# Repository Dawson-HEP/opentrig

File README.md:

# opentrig

> ***open***-source ***trig***ger system

An open-source, integrated, particle physics data acquisition system (DAQ).

Designed to interface with timing systems controlled by the [AIDA-2020 TLU](https://gitlab.com/ohwr/project/fmc-mtlu).
Up to 24 digital trigger channels with variable-gain threshold setting.

## Features

- 144 MHz internal FPGA clock, and timing resolution
- 24 digital trigger channels with variable gain
- Input voltage range 3.3V-5V
- TTL level compatible clock, trigger, input and output
- [AIDA-2020 TLU synchronous AIDA mode](https://gitlab.com/ohwr/project/fmc-mtlu/-/raw/master/Documentation/Main_TLU.pdf?ref_type=heads) (page 31) compatible FPGA

## Hardware Overview

[**Schematics can be found here.**](hardware/digital.pdf)

Front panel IO (left)
- Input clock signal (<40 MHz square wave)
- Output clock signal (120 MHz square wave, 3.3V TTL, <0.5% jitter, phase-locked)
- Input/output trigger (3.3V TTL)
- Input/output veto (3.3V TTL)
- Extra 50R impedance-matched inputs

Back panel (right)
- 24 channel digital inputs, with variable trigger thresholds (1.024 mV steps):
    - 0.000V-2.000V (1x gain)
    - 0.000V-4.000V (2x gain)

Internal components
- Low drift 5.000V reference (TI REF5050AIR)
- 12 high-speed thresholding comparators (TI TLV3502)
- 120 MHz MCU (RP2040)
- FPGA (Lattice ICE40 HX4K)

## Trigger Architecture

The *opentrig* system is a 24-channel, synchronous data acquisition platform compatible with EUDAQ2-compatible beamline trigger systems. Each channel digitizes an analog falling-edge into a digital rising-edge depending on a threshold set by independent digital-to-analog converters (DACs). Three trigger sources are fed into a selectable OR-ing gate, which allows for the selection of the interrupt source(s) for sample recording.

The trigger combiner vetoes priority in regards to the inputs of selected trigger sources, and assigns FPGA SPI bandwidth to the microcontroller (MCU) for processing and sampling. An active-high trigger output is asserted with controllable duration and delay in reference to the trigger sources. The sample interrupt interacts with the MCU in order to stream data live through the USB Type-C interface across bulk transfer.

### Trigger Delay

The delays incurred by the trigger is synchronized across channels by means of length matching. The largest skew is a result of level shifting: indeed up to $\pm 0.3$ ns across channels. No significant differences are measured in practice. FPGA gate skew is below the delays of level shifting, and are thus negligible in practice. PCB traces are delay-matched to within $\pm0.01$ mm. Given the assumption that channels are synchronized between each other, the input-output delay needs to be considered.

## Clocks

The FPGA PLL is synchronized to a sampling clock of $120$ MHz, while the SPI clock transfers data at a rate of $5$ MHz. The user can select an internal clock input or an external clock input, both requiring different PLL clock dividers to achieve the full sampling rate at $120$ Msps.

Clocks are phase-aligned by phase-locked-loop (PLL). An internal clock can be generated for the independent functioning of the DAQ. Proper PLL clock dividers and multipliers must be set to achieve the target $120$ MHz. An external clock compliant to EUDAQ2 trigger systems, such as the AIDA-2020 TLU, can be synchronized to \textit{opentrig}. A 16-bit trigger-ID can be read synchronously by the phase-locked external trigger module, which will be recorded upon the assertion of a sample interrupt.

## Voltage Levels

The 24 analog inputs are limited to a voltage range of $-0.30$ V to $+5.30$ V on wide-gain mode, and $-0.30$ V to $+3.30$ V on limited-gain mode. A voltage beyond permissible levels may cause irreversible damage to thresholding comparators, whose inputs are directly connected to SMA connectors.

The digital signals are high-impedance or $50 \Omega$ terminated depending on the label, and function on $3.3$ V CMOS voltage levels. The push-pull drivers have weak drive capabilities; therefore, only small digital loads may be attached with matched impedance.

## Directory Structure

The hardware is designed in [KiCad](https://www.kicad.org/) for the digital trigger front-end and mechanical layout, while the firmware and control utilities are written in [Rust](https://rust-lang.org/) using the [Embassy](https://embassy.dev/) embedded framework. The FPGA subsystems are written in pure Verilog with the [Yosys](https://github.com/YosysHQ/yosys.git) open-source toolchain, and [Project Icestorm](https://github.com/YosysHQ/icestorm)'s bitstream documentation.

```
opentrig/
├── hardware/ # KiCad hardware design
│   ├── fab/ # Fabrication files and gerbers
│   ├── logos.pretty/ # Custom logo footprints and graphics
│   └── digital.pretty/ # Custom digital footprints and component libraries
│
├── opentrig/ # Core DAQ firmware
│   ├── src/ # Source code (Rust + Embassy)
│   │   └── fpga/ # FPGA interface and logic modules
│   └── target/ # Compiled firmware output and build artifacts
│
├── cli/ # Command-line interface for control and configuration via host computer
│   ├── src/ # Rust source for CLI utilities
│   └── target/ # Compiled CLI binaries
│
├── tests/ # Automated and hardware-in-the-loop test framework
│   ├── src/ # Unit and integration test sources
│   └── target/ # Compiled test binaries and reports
│
└── README.md # Project overview, setup, and usage instructions
```

## Building

Before building the firmware and FPGA bitstream, you need to install a few dependencies for Rust and the FPGA toolchain. Follow these steps:

- Install [Rust](https://www.rust-lang.org/) – the firmware is written in Rust using the Embassy framework.
- Install [Just](https://github.com/casey/just) – used to run the build commands.
- Install [Yosys](https://github.com/YosysHQ/yosys) – for Verilog synthesis of the FPGA.
- Install [Project Icestorm](https://github.com/YosysHQ/icestorm) tools – for routing and bitstream generation for iCE40 FPGAs.
- Optional: [KiCad](https://www.kicad.org/) – for viewing and editing hardware schematics.

Once dependencies are installed, clone the repository, navigate to the firmware folder, and run the build commands:

```bash
# Clone the Protovolt repository from GitHub
git clone https://github.com/Dawson-HEP/opentrig.git

# Go to firmware directory
cd opentrig/opentrig
```

```bash
# Compile verilog bitstream
just build-verilog

# Compile embedded firmware
just build-rust
```

Flashing:
- SWD debug port on the PCB
- USB flashing via data port

## Running the DAQ
A USB Type-C Power Delivery (PD) supply must be connected to the power connector to bias analog and digital circuitry. A $100$ W-capable supply with $20$V output is preferred to provide enough margin for buck converters and analog filtering supplies to function properly. A digital data cable links the data acquisition computer with the DAQ.

## Debugging the DAQ
Three SWD debug interfaces are made available to the user: the main *opentrig* MCU debug link, the simulation PICO link, and the logic analyzer PICO link. The MCU flash process includes the FPGA bitstream, which is written upon power up of the DAQ. The simulation PICO, when powered, produce triggers via the internal links directly to the FPGA, which allows for programmatic debugging. The logic analyzer serves as a bitstream debugger, where internal registers and wires can be sampled.

## DESY Test Beam

The interfacing with the AIDA-2020 TLU functionality has been verified at the [DESY II Test Beam facility](https://desy.de/index_eng.html) in September of 2025, as part of the [Beamline for Schools](https://beamlineforschools.cern/) Competition. 

*Testbeam Area 21, Translation Stage*

## Gallery

## License

This project is open-source under the Eclipse Public License - v 2.0.

## Authors

- [Tian Yi, Xia](https://github.com/ThatAquarel), xtxiatianyi@gmail.com
- [Leandro Perez-Moran](https://github.com/LudioRex), pemle2007@gmail.com

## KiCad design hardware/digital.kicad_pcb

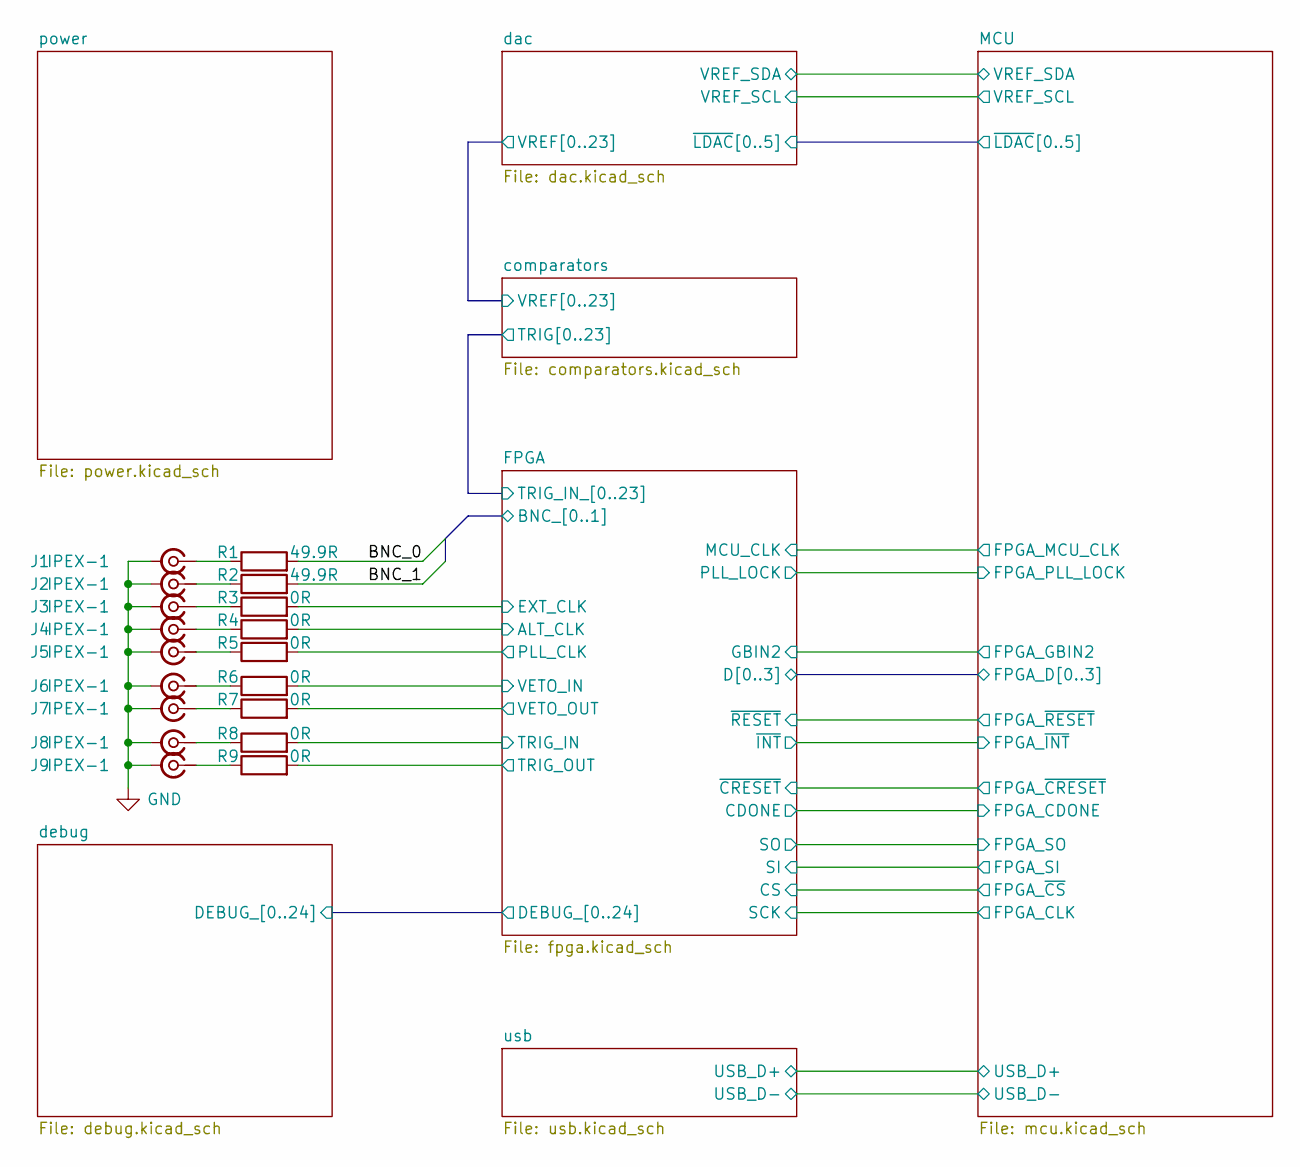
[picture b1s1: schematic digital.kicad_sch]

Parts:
J1, J2, J3, J4, J5, J6, J7, J8, J9: IPEX-1; BWIPX-1-001E; LCSC C496552
R1, R2: 49.9R; R_0402_1005Metric; LCSC C17168
R3, R4, R5, R6, R7, R8, R9: 0R; R_0402_1005Metric; LCSC C17168

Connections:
/FPGA/ALT_CLK: R4.2; also elsewhere on the board
/FPGA/BNC_0: R1.2; also elsewhere on the board
/FPGA/BNC_1: R2.2; also elsewhere on the board
/FPGA/EXT_CLK: R3.2; also elsewhere on the board
/FPGA/PLL_CLK: R5.2; also elsewhere on the board
/FPGA/TRIG_IN: R8.2; also elsewhere on the board
/FPGA/TRIG_OUT: R9.2; also elsewhere on the board
/FPGA/VETO_IN: R6.2; also elsewhere on the board
/FPGA/VETO_OUT: R7.2; also elsewhere on the board
GND: J1.2 (Ext), J2.2 (Ext), J3.2 (Ext), J4.2 (Ext), J5.2 (Ext), J6.2 (Ext), J7.2 (Ext), J8.2 (Ext), J9.2 (Ext); also elsewhere on the board
unnamed: J1.1 (In), R1.1
unnamed: J2.1 (In), R2.1
unnamed: J3.1 (In), R3.1
unnamed: J4.1 (In), R4.1
unnamed: J5.1 (In), R5.1
unnamed: J6.1 (In), R6.1
unnamed: J7.1 (In), R7.1
unnamed: J8.1 (In), R8.1
unnamed: J9.1 (In), R9.1

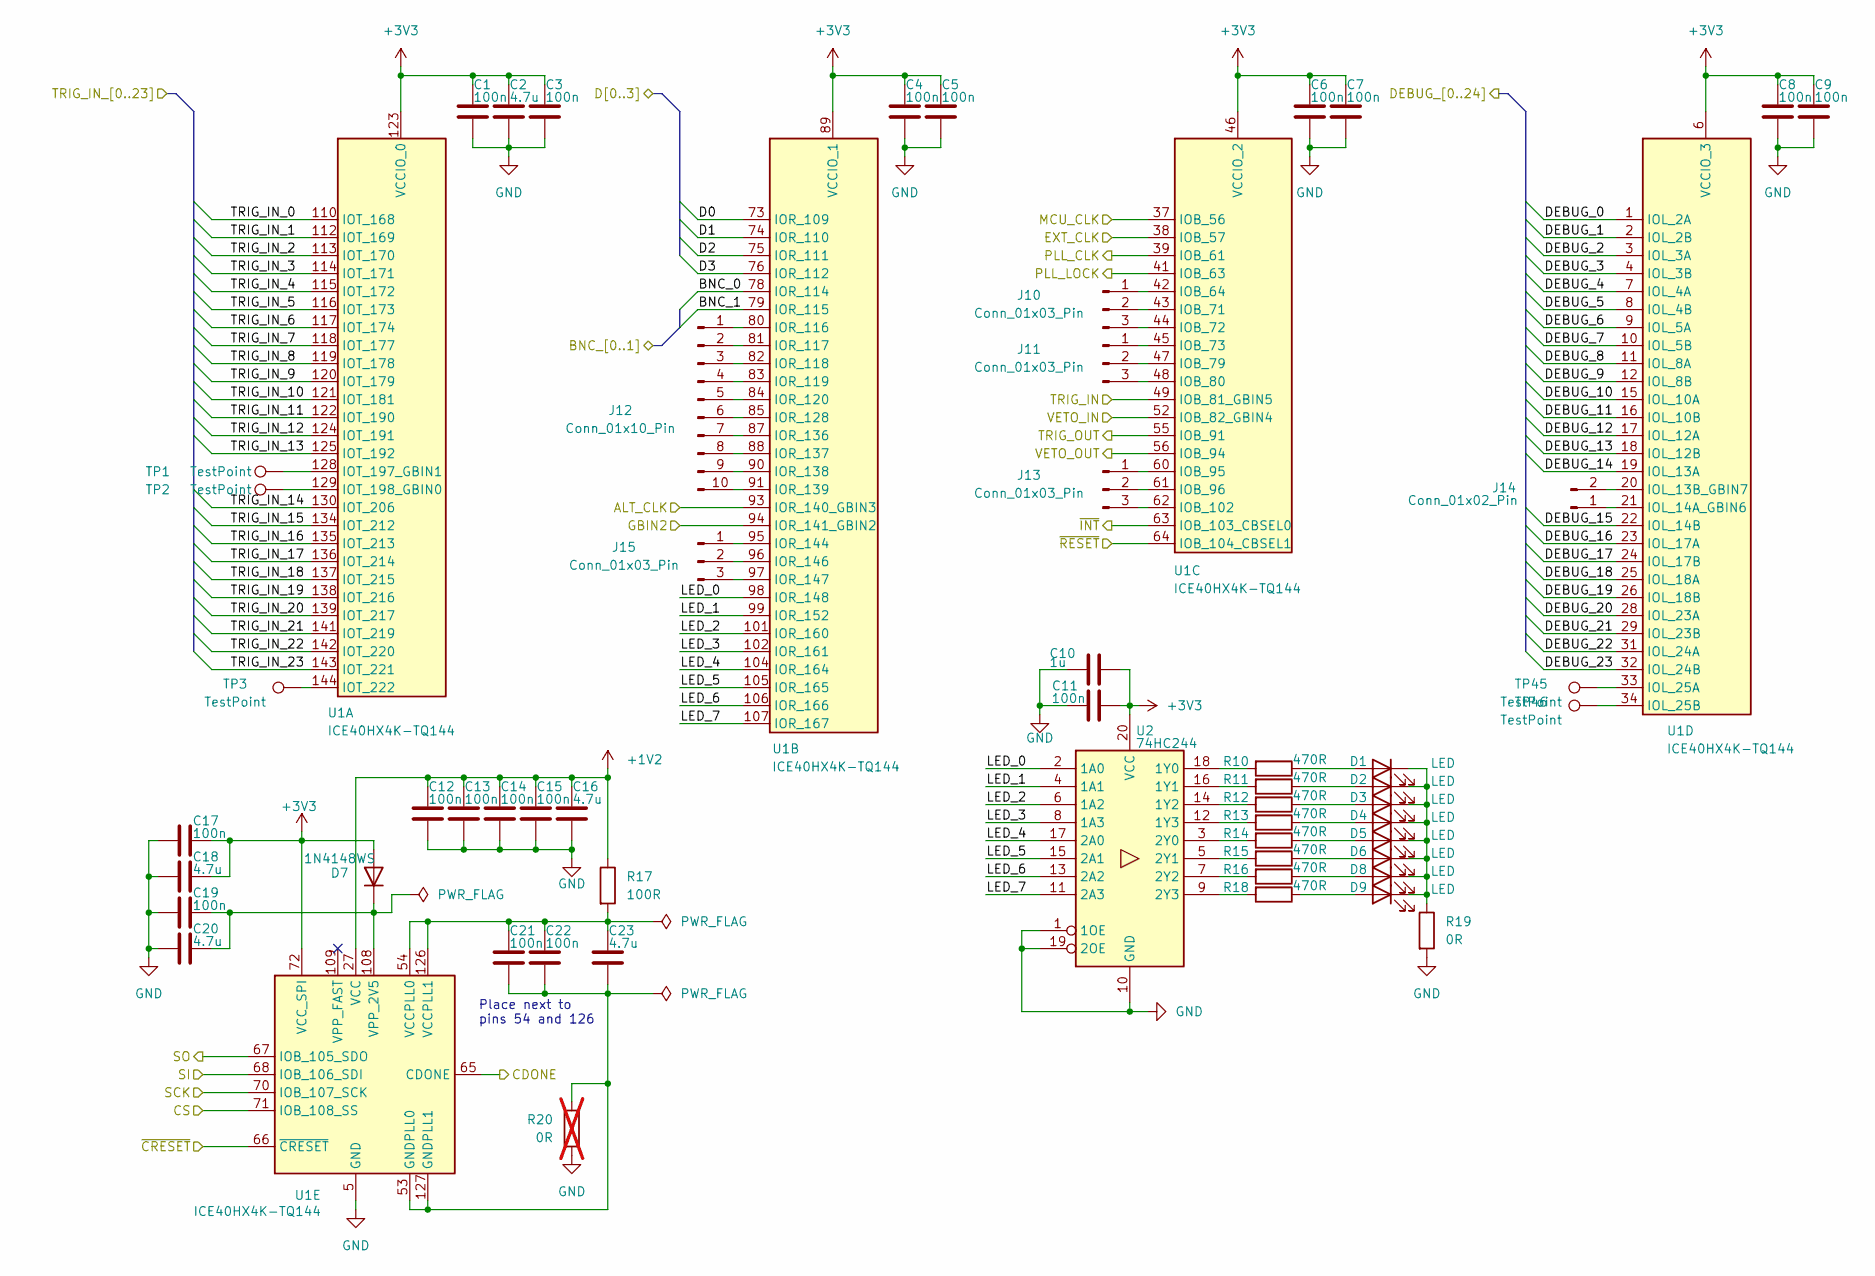
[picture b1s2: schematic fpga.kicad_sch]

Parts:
C1, C3, C4, C5, C6, C7, C8, C9, C11, C12, C13, C14, C15, C17, C19, C21, C22: 100n; C_0402_1005Metric; LCSC C307331
C2, C16, C18, C20, C23: 4.7u; C_1206_3216Metric; LCSC C29823
C10: 1u; C_0805_2012Metric; LCSC C28323
D1, D2, D3, D4, D5, D6, D8, D9: LED; LED_0805_2012Metric; LCSC C2297
D7: 1N4148WS; D_SOD-323; LCSC C2128
J10, J11, J13, J15: Conn_01x03_Pin; PinHeader_1x03_P1.00mm_Vertical_SMD_Pin1Left
J12: Conn_01x10_Pin; PinHeader_1x10_P1.00mm_Vertical_SMD_Pin1Left
J14: Conn_01x02_Pin; PinHeader_1x02_P1.00mm_Vertical_SMD_Pin1Left
R10, R11, R12, R13, R14, R15, R16, R18: 470R; R_0402_1005Metric; LCSC C25117
R17: 100R; R_0402_1005Metric; LCSC C25076
R19: 0R; R_0402_1005Metric; LCSC C17168
R20: 0R; R_0402_1005Metric; not fitted
TP1, TP2, TP3, TP45, TP46: TestPoint; TestPoint_Pad_D1.0mm
U1: ICE40HX4K-TQ144; TQFP-144_20x20mm_P0.5mm
U2: 74HC244; TSSOP-20_4.4x6.5mm_P0.65mm; LCSC C6835

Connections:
+1V2: C12.1, C13.1, C14.1, C15.1, C16.1, R17.1, U1.27 (VCC), U1.40 (VCC), U1.92 (VCC), U1.111 (VCC); also elsewhere on the board
+3V3: C1.1, C2.1, C3.1, C4.1, C5.1, C6.1, C7.1, C8.1, C9.1, C10.2, C11.2, C17.1, C18.1, D7.2 (A), U1.6 (VCCIO_3), U1.30 (VCCIO_3), U1.46 (VCCIO_2), U1.57 (VCCIO_2), U1.72 (VCC_SPI), U1.89 (VCCIO_1), U1.100 (VCCIO_1), U1.123 (VCCIO_0), U1.131 (VCCIO_0), U2.20 (VCC); also elsewhere on the board
/FPGA/ALT_CLK: U1.93 (IOR_140_GBIN3); also elsewhere on the board
/FPGA/BNC_0: U1.78 (IOR_114); also elsewhere on the board
/FPGA/BNC_1: U1.79 (IOR_115); also elsewhere on the board
/FPGA/CDONE: U1.65 (CDONE); also elsewhere on the board
/FPGA/CS: U1.71 (IOB_108_SS); also elsewhere on the board
/FPGA/D0: U1.73 (IOR_109); also elsewhere on the board
/FPGA/D1: U1.74 (IOR_110); also elsewhere on the board
/FPGA/D2: U1.75 (IOR_111); also elsewhere on the board
/FPGA/D3: U1.76 (IOR_112); also elsewhere on the board
/FPGA/DEBUG_0: U1.1 (IOL_2A); also elsewhere on the board
/FPGA/DEBUG_1: U1.2 (IOL_2B); also elsewhere on the board
/FPGA/DEBUG_2: U1.3 (IOL_3A); also elsewhere on the board
/FPGA/DEBUG_3: U1.4 (IOL_3B); also elsewhere on the board
/FPGA/DEBUG_4: U1.7 (IOL_4A); also elsewhere on the board
/FPGA/DEBUG_5: U1.8 (IOL_4B); also elsewhere on the board
/FPGA/DEBUG_6: U1.9 (IOL_5A); also elsewhere on the board
/FPGA/DEBUG_7: U1.10 (IOL_5B); also elsewhere on the board
/FPGA/DEBUG_8: U1.11 (IOL_8A); also elsewhere on the board
/FPGA/DEBUG_9: U1.12 (IOL_8B); also elsewhere on the board
/FPGA/DEBUG_10: U1.15 (IOL_10A); also elsewhere on the board
/FPGA/DEBUG_11: U1.16 (IOL_10B); also elsewhere on the board
/FPGA/DEBUG_12: U1.17 (IOL_12A); also elsewhere on the board
/FPGA/DEBUG_13: U1.18 (IOL_12B); also elsewhere on the board
/FPGA/DEBUG_14: U1.19 (IOL_13A); also elsewhere on the board
/FPGA/DEBUG_15: U1.22 (IOL_14B); also elsewhere on the board
/FPGA/DEBUG_16: U1.23 (IOL_17A); also elsewhere on the board
/FPGA/DEBUG_17: U1.24 (IOL_17B); also elsewhere on the board
/FPGA/DEBUG_18: U1.25 (IOL_18A); also elsewhere on the board
/FPGA/DEBUG_19: U1.26 (IOL_18B); also elsewhere on the board
/FPGA/DEBUG_20: U1.28 (IOL_23A); also elsewhere on the board
/FPGA/DEBUG_21: U1.29 (IOL_23B); also elsewhere on the board
/FPGA/DEBUG_22: U1.31 (IOL_24A); also elsewhere on the board
/FPGA/DEBUG_23: U1.32 (IOL_24B); also elsewhere on the board
/FPGA/EXT_CLK: U1.38 (IOB_57); also elsewhere on the board
/FPGA/GBIN2: U1.94 (IOR_141_GBIN2); also elsewhere on the board
/FPGA/LED_0: U1.98 (IOR_148), U2.2 (1A0)
/FPGA/LED_1: U1.99 (IOR_152), U2.4 (1A1)
/FPGA/LED_2: U1.101 (IOR_160), U2.6 (1A2)
/FPGA/LED_3: U1.102 (IOR_161), U2.8 (1A3)
/FPGA/LED_4: U1.104 (IOR_164), U2.17 (2A0)
/FPGA/LED_5: U1.105 (IOR_165), U2.15 (2A1)
/FPGA/LED_6: U1.106 (IOR_166), U2.13 (2A2)
/FPGA/LED_7: U1.107 (IOR_167), U2.11 (2A3)
/FPGA/MCU_CLK: U1.37 (IOB_56); also elsewhere on the board
/FPGA/PLL_CLK: U1.39 (IOB_61); also elsewhere on the board
/FPGA/PLL_LOCK: U1.41 (IOB_63); also elsewhere on the board
/FPGA/SCK: U1.70 (IOB_107_SCK); also elsewhere on the board
/FPGA/SI: U1.68 (IOB_106_SDI); also elsewhere on the board
/FPGA/SO: U1.67 (IOB_105_SDO); also elsewhere on the board
/FPGA/TRIG_IN: U1.49 (IOB_81_GBIN5); also elsewhere on the board
/FPGA/TRIG_IN_0: U1.110 (IOT_168); also elsewhere on the board
/FPGA/TRIG_IN_1: U1.112 (IOT_169); also elsewhere on the board
/FPGA/TRIG_IN_2: U1.113 (IOT_170); also elsewhere on the board
/FPGA/TRIG_IN_3: U1.114 (IOT_171); also elsewhere on the board
/FPGA/TRIG_IN_4: U1.115 (IOT_172); also elsewhere on the board
/FPGA/TRIG_IN_5: U1.116 (IOT_173); also elsewhere on the board
/FPGA/TRIG_IN_6: U1.117 (IOT_174); also elsewhere on the board
/FPGA/TRIG_IN_7: U1.118 (IOT_177); also elsewhere on the board
/FPGA/TRIG_IN_8: U1.119 (IOT_178); also elsewhere on the board
/FPGA/TRIG_IN_9: U1.120 (IOT_179); also elsewhere on the board
/FPGA/TRIG_IN_10: U1.121 (IOT_181); also elsewhere on the board
/FPGA/TRIG_IN_11: U1.122 (IOT_190); also elsewhere on the board
/FPGA/TRIG_IN_12: U1.124 (IOT_191); also elsewhere on the board
/FPGA/TRIG_IN_13: U1.125 (IOT_192); also elsewhere on the board
/FPGA/TRIG_IN_14: U1.130 (IOT_206); also elsewhere on the board
/FPGA/TRIG_IN_15: U1.134 (IOT_212); also elsewhere on the board
/FPGA/TRIG_IN_16: U1.135 (IOT_213); also elsewhere on the board
/FPGA/TRIG_IN_17: U1.136 (IOT_214); also elsewhere on the board
/FPGA/TRIG_IN_18: U1.137 (IOT_215); also elsewhere on the board
/FPGA/TRIG_IN_19: U1.138 (IOT_216); also elsewhere on the board
/FPGA/TRIG_IN_20: U1.139 (IOT_217); also elsewhere on the board
/FPGA/TRIG_IN_21: U1.141 (IOT_219); also elsewhere on the board
/FPGA/TRIG_IN_22: U1.142 (IOT_220); also elsewhere on the board
/FPGA/TRIG_IN_23: U1.143 (IOT_221); also elsewhere on the board
/FPGA/TRIG_OUT: U1.55 (IOB_91); also elsewhere on the board
/FPGA/VETO_IN: U1.52 (IOB_82_GBIN4); also elsewhere on the board
/FPGA/VETO_OUT: U1.56 (IOB_94); also elsewhere on the board
/FPGA/~CRESET: U1.66 (~CRESET); also elsewhere on the board
/FPGA/~INT: U1.63 (IOB_103_CBSEL0); also elsewhere on the board
/FPGA/~RESET: U1.64 (IOB_104_CBSEL1); also elsewhere on the board
GND: C1.2, C2.2, C3.2, C4.2, C5.2, C6.2, C7.2, C8.2, C9.2, C10.1, C11.1, C12.2, C13.2, C14.2, C15.2, C16.2, C17.2, C18.2, C19.2, C20.2, R19.2, R20.2, U1.5 (GND), U1.13 (GND), U1.14 (GND), U1.59 (GND), U1.69 (GND), U1.86 (GND), U1.103 (GND), U1.132 (GND), U1.140 (GND), U2.1 (1OE), U2.10 (GND), U2.19 (2OE); also elsewhere on the board
unnamed: D1.2 (A), R10.1
unnamed: D1.1 (K), D2.1 (K), D3.1 (K), D4.1 (K), D5.1 (K), D6.1 (K), D8.1 (K), D9.1 (K), R19.1
unnamed: D2.2 (A), R11.1
unnamed: D3.2 (A), R12.1
unnamed: D4.2 (A), R13.1
unnamed: D5.2 (A), R14.1
unnamed: D6.2 (A), R15.1
unnamed: C19.1, C20.1, D7.1 (K), U1.108 (VPP_2V5)
unnamed: D8.2 (A), R16.1
unnamed: D9.2 (A), R18.1
unnamed: J10.1, U1.42 (IOB_64)
unnamed: J10.2, U1.43 (IOB_71)
unnamed: J10.3, U1.44 (IOB_72)
unnamed: J11.1, U1.45 (IOB_73)
unnamed: J11.2, U1.47 (IOB_79)
unnamed: J11.3, U1.48 (IOB_80)
unnamed: J12.1, U1.80 (IOR_116)
unnamed: J12.2, U1.81 (IOR_117)
unnamed: J12.3, U1.82 (IOR_118)
unnamed: J12.4, U1.83 (IOR_119)
unnamed: J12.5, U1.84 (IOR_120)
unnamed: J12.6, U1.85 (IOR_128)
unnamed: J12.7, U1.87 (IOR_136)
unnamed: J12.8, U1.88 (IOR_137)
unnamed: J12.9, U1.90 (IOR_138)
unnamed: J12.10, U1.91 (IOR_139)
unnamed: J13.1, U1.60 (IOB_95)
unnamed: J13.2, U1.61 (IOB_96)
unnamed: J13.3, U1.62 (IOB_102)
unnamed: J14.1, U1.21 (IOL_14A_GBIN6)
unnamed: J14.2, U1.20 (IOL_13B_GBIN7)
unnamed: J15.1, U1.95 (IOR_144)
unnamed: J15.2, U1.96 (IOR_146)
unnamed: J15.3, U1.97 (IOR_147)
unnamed: TP1.1, U1.128 (IOT_197_GBIN1)
unnamed: TP2.1, U1.129 (IOT_198_GBIN0)
unnamed: TP3.1, U1.144 (IOT_222)
unnamed: TP45.1, U1.33 (IOL_25A)
unnamed: TP46.1, U1.34 (IOL_25B)
unnamed: C21.2, C22.2, C23.2, R20.1, U1.53 (GNDPLL0), U1.127 (GNDPLL1)
unnamed: C21.1, C22.1, C23.1, R17.2, U1.54 (VCCPLL0), U1.126 (VCCPLL1)
unnamed: R10.2, U2.18 (1Y0)
unnamed: R11.2, U2.16 (1Y1)
unnamed: R12.2, U2.14 (1Y2)
unnamed: R13.2, U2.12 (1Y3)
unnamed: R14.2, U2.3 (2Y0)
unnamed: R15.2, U2.5 (2Y1)
unnamed: R16.2, U2.7 (2Y2)
unnamed: R18.2, U2.9 (2Y3)

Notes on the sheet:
Place next to pins 54 and 126

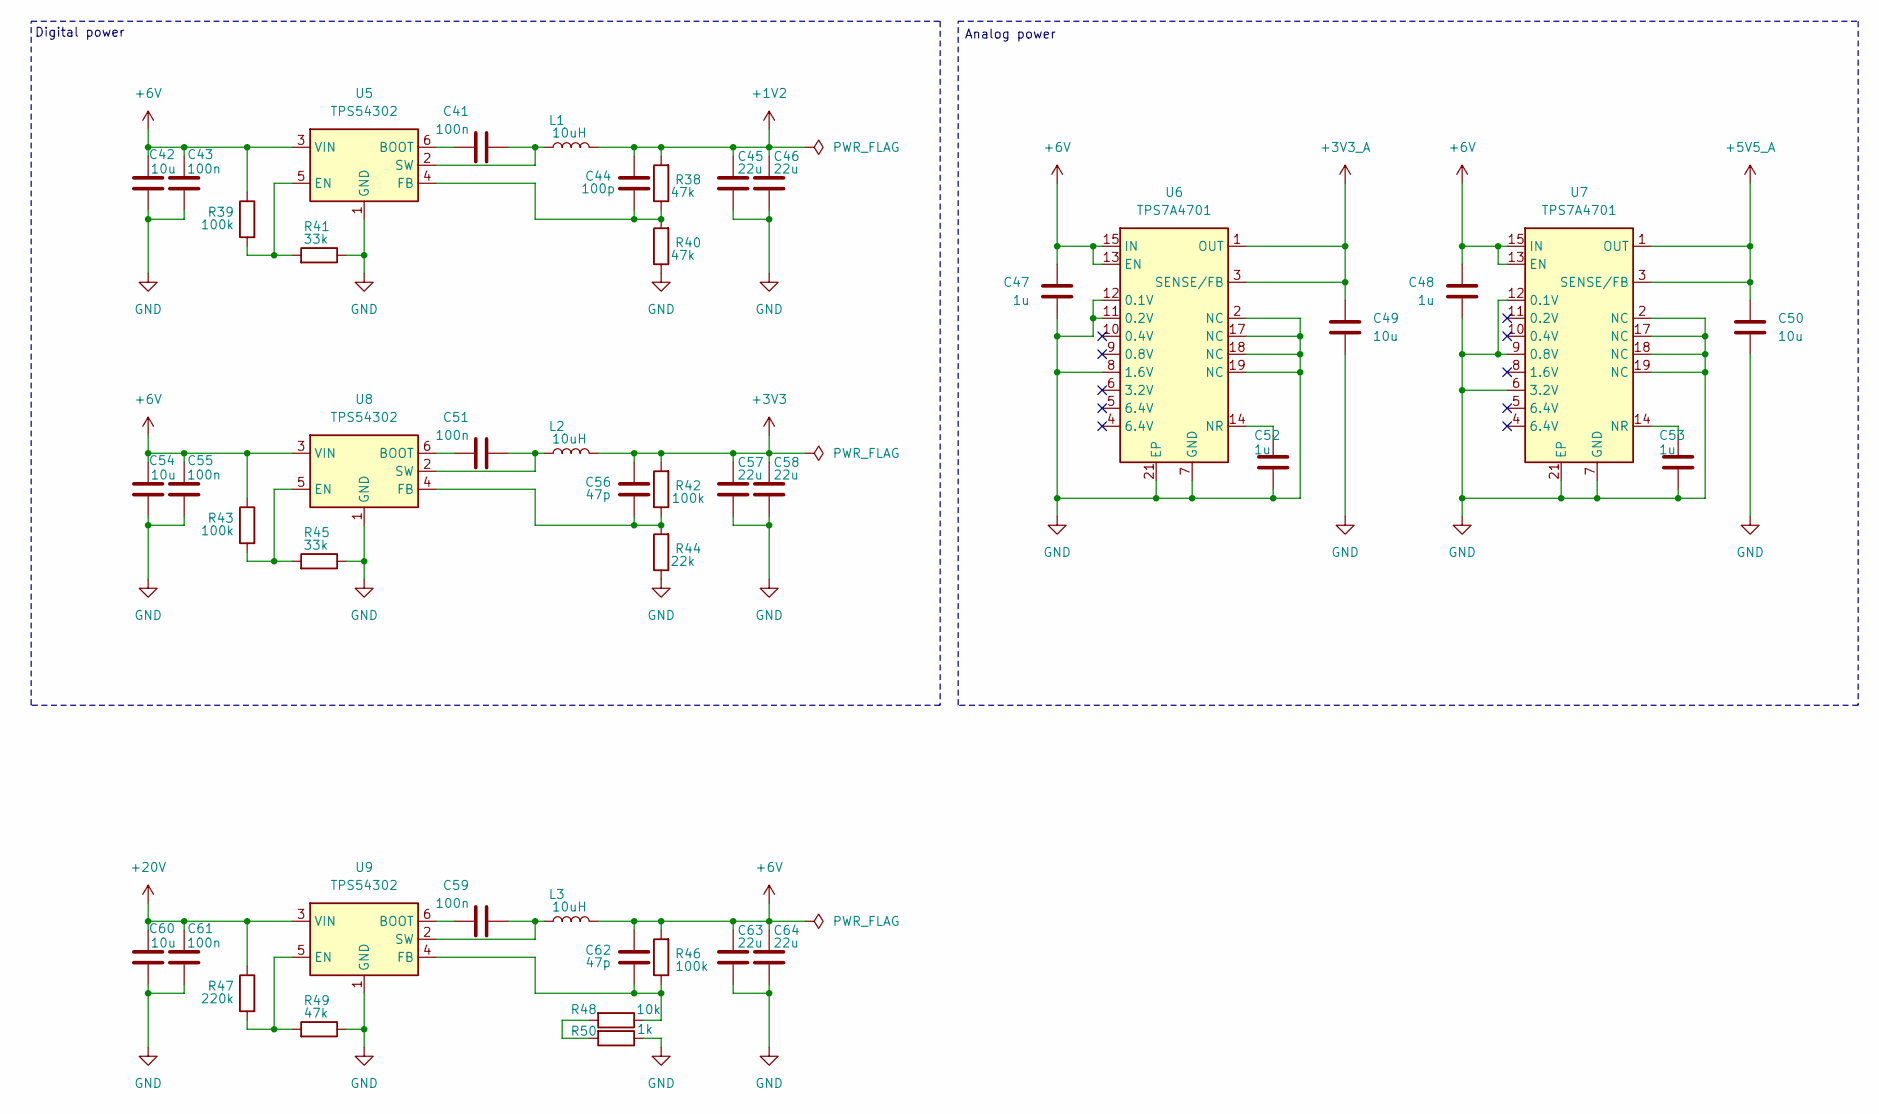
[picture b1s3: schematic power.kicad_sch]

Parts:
C41, C43, C51, C55, C59, C61: 100n; C_0402_1005Metric; LCSC C307331
C42, C49, C50, C54, C60: 10u; C_1206_3216Metric; LCSC C13585
C44: 100p; C_0402_1005Metric; LCSC C1567
C45, C46, C57, C58, C63, C64: 22u; C_0603_1608Metric; LCSC C59461
C47, C48, C52, C53: 1u; C_0805_2012Metric; LCSC C28323
C56, C62: 47p; C_0402_1005Metric; LCSC C1567
L1, L2, L3: 10uH; L_Changjiang_FXL0630; LCSC C167223
R38, R40, R49: 47k; R_0402_1005Metric; LCSC C25792
R39, R43: 100k; R_0603_1608Metric; LCSC C22961
R41, R45: 33k; R_0402_1005Metric; LCSC C25792
R42, R46: 100k; R_0402_1005Metric; LCSC C25741
R44: 22k; R_0402_1005Metric; LCSC C25768
R47: 220k; R_0603_1608Metric; LCSC C22961
R48: 10k; R_0402_1005Metric; LCSC C25744
R50: 1k; R_0402_1005Metric; LCSC C11702
U5, U8, U9: TPS54302; SOT-23-6; LCSC C129370
U6, U7: TPS7A4701; Texas_RGW0020A_VQFN-20-1EP_5x5mm_P0.65mm_EP3.15x3.15mm_Ther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; LCSC C90084

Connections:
+1V2: C44.2, C45.2, C46.2, L1.2, R38.2; also elsewhere on the board
+3V3: C56.2, C57.2, C58.2, L2.2, R42.2; also elsewhere on the board
+3V3_A: C49.1, U6.1 (OUT), U6.3 (SENSE/FB), U6.20 (OUT); also elsewhere on the board
+5V5_A: C50.1, U7.1 (OUT), U7.3 (SENSE/FB), U7.20 (OUT); also elsewhere on the board
+6V: C42.1, C43.2, C47.1, C48.1, C54.1, C55.2, C62.2, C63.2, C64.2, L3.2, R39.1, R43.1, R46.2, U5.3 (VIN), U6.13 (EN), U6.15 (IN), U6.16 (IN), U7.13 (EN), U7.15 (IN), U7.16 (IN), U8.3 (VIN)
+20V: C60.1, C61.2, R47.1, U9.3 (VIN); also elsewhere on the board
GND: C42.2, C43.1, C45.1, C46.1, C47.2, C48.2, C49.2, C50.2, C52.2, C53.2, C54.2, C55.1, C57.1, C58.1, C60.2, C61.1, C63.1, C64.1, R40.1, R41.1, R44.1, R45.1, R49.1, R50.1, U5.1 (GND), U6.2 (NC), U6.7 (GND), U6.8 (1.6V), U6.11 (0.2V), U6.12 (0.1V), U6.17 (NC), U6.18 (NC), U6.19 (NC), U6.21 (EP), U7.2 (NC), U7.6 (3.2V), U7.7 (GND), U7.9 (0.8V), U7.12 (0.1V), U7.17 (NC), U7.18 (NC), U7.19 (NC), U7.21 (EP), U8.1 (GND), U9.1 (GND); also elsewhere on the board
unnamed: R48.2, R50.2
unnamed: C41.1, U5.6 (BOOT)
unnamed: R39.2, R41.2, U5.5 (EN)
unnamed: C44.1, R38.1, R40.2, U5.4 (FB)
unnamed: C41.2, L1.1, U5.2 (SW)
unnamed: C52.1, U6.14 (NR)
unnamed: C53.1, U7.14 (NR)
unnamed: C51.1, U8.6 (BOOT)
unnamed: R43.2, R45.2, U8.5 (EN)
unnamed: C56.1, R42.1, R44.2, U8.4 (FB)
unnamed: C51.2, L2.1, U8.2 (SW)
unnamed: C59.1, U9.6 (BOOT)
unnamed: R47.2, R49.2, U9.5 (EN)
unnamed: C62.1, R46.1, R48.1, U9.4 (FB)
unnamed: C59.2, L3.1, U9.2 (SW)

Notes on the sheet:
Analog power
Digital power

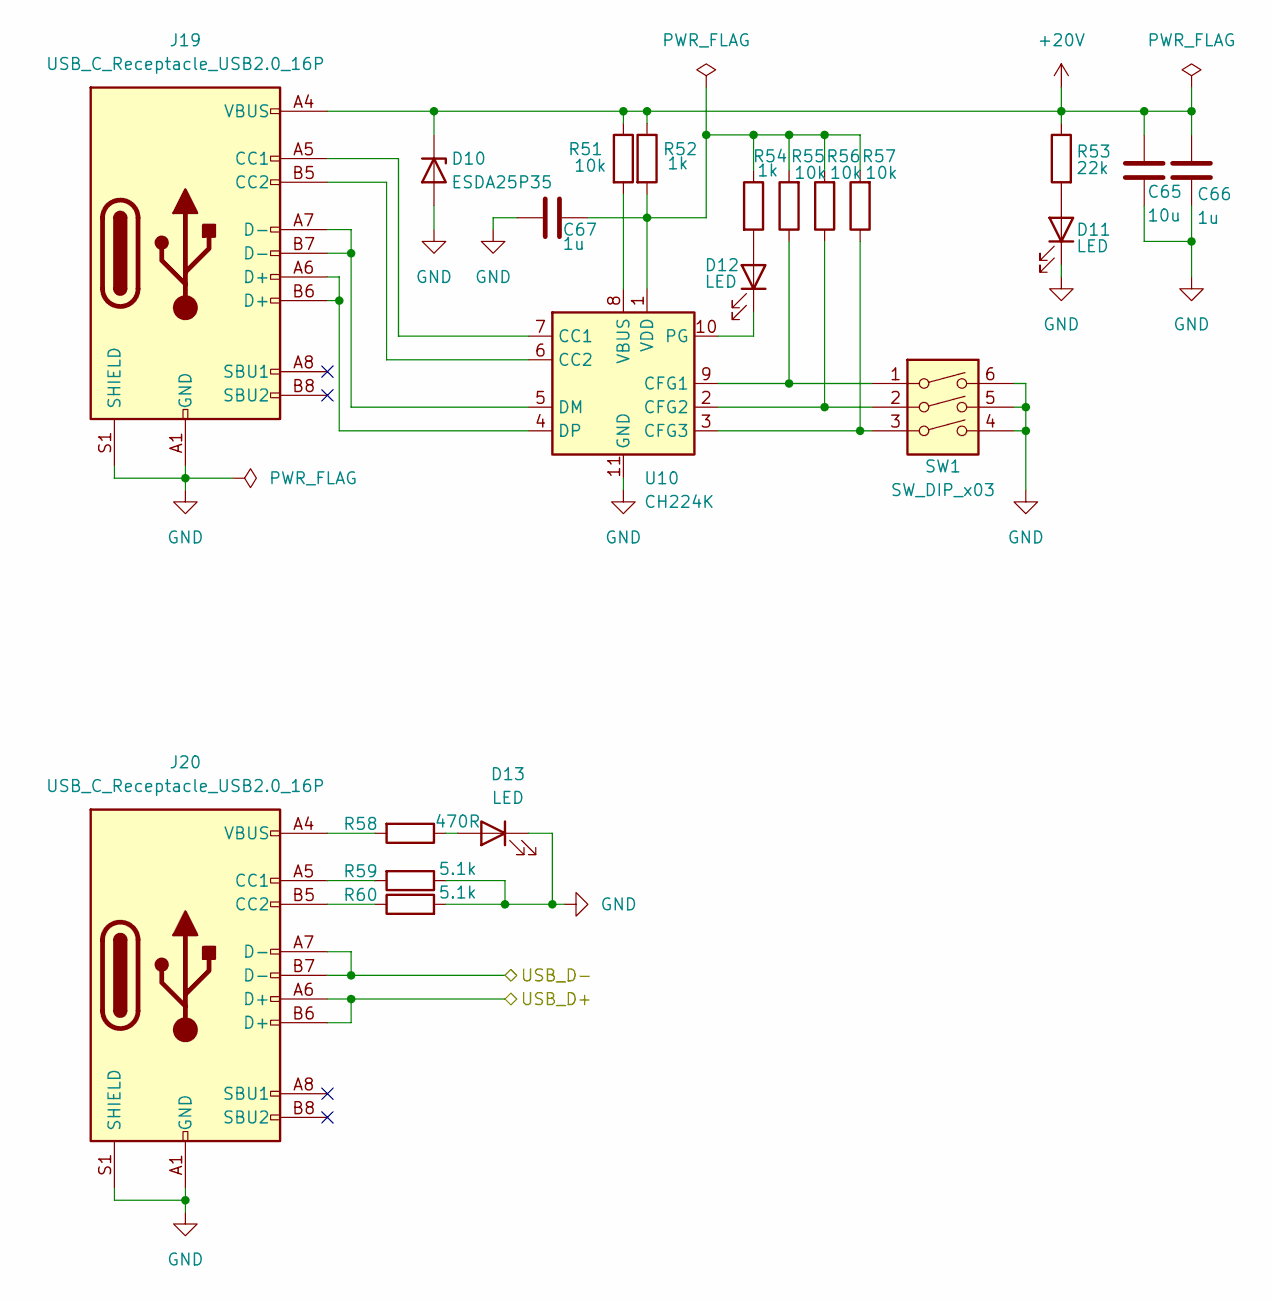
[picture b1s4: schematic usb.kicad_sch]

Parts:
C65: 10u; C_1206_3216Metric; LCSC C13585
C66, C67: 1u; C_0805_2012Metric; LCSC C28323
D10: ESDA25P35; D_1610_4027Metric; LCSC C1974707
D11, D12, D13: LED; LED_0805_2012Metric; LCSC C2297
J19, J20: USB_C_Receptacle_USB2.0_16P; USB_C_Receptacle_GCT_USB4105-xx-A_16P_TopMnt_Horizontal; LCSC C165948
R51, R55, R56, R57: 10k; R_0402_1005Metric; LCSC C25744
R52, R54: 1k; R_0402_1005Metric; LCSC C11702
R53: 22k; R_0402_1005Metric; LCSC C25768
R58: 470R; R_0402_1005Metric; LCSC C25117
R59, R60: 5.1k; R_0402_1005Metric; LCSC C25905
SW1: SW_DIP_x03; SW_DIP_SPSTx03_Slide_6.7x9.18mm_W8.61mm_P2.54mm_LowProfile; LCSC C129079
U10: CH224K; SSOP-10-1EP_3.9x4.9mm_P1mm_EP2.1x3.3mm; LCSC C970725

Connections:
+20V: C65.1, C66.1, D10.1 (K), J19.A4 (VBUS), J19.A9 (VBUS), J19.B4 (VBUS), J19.B9 (VBUS), R51.1, R52.1, R53.1; also elsewhere on the board
/MCU/USB_D+: J20.A6 (D+), J20.B6 (D+); also elsewhere on the board
/MCU/USB_D-: J20.A7 (D-), J20.B7 (D-); also elsewhere on the board
GND: C65.2, C66.2, C67.2, D10.2 (A), D11.1 (K), D13.1 (K), J19.A1 (GND), J19.A12 (GND), J19.B1 (GND), J19.B12 (GND), J19.S1 (SHIELD), J20.A1 (GND), J20.A12 (GND), J20.B1 (GND), J20.B12 (GND), J20.S1 (SHIELD), R59.1, R60.2, SW1.4, SW1.5, SW1.6, U10.11 (GND); also elsewhere on the board
unnamed: D11.2 (A), R53.2
unnamed: D12.2 (A), R54.2
unnamed: D12.1 (K), U10.10 (PG)
unnamed: D13.2 (A), R58.1
unnamed: J19.A5 (CC1), U10.7 (CC1)
unnamed: J19.B5 (CC2), U10.6 (CC2)
unnamed: J20.A5 (CC1), R59.2
unnamed: J20.B5 (CC2), R60.1
unnamed: J20.A4 (VBUS), J20.A9 (VBUS), J20.B4 (VBUS), J20.B9 (VBUS), R58.2
unnamed: R55.1, SW1.1, U10.9 (CFG1)
unnamed: R56.1, SW1.2, U10.2 (CFG2)
unnamed: R57.1, SW1.3, U10.3 (CFG3)
unnamed: J19.A7 (D-), J19.B7 (D-), U10.5 (DM)
unnamed: J19.A6 (D+), J19.B6 (D+), U10.4 (DP)
unnamed: R51.2, U10.8 (VBUS)
unnamed: C67.1, R52.2, R54.1, R55.2, R56.2, R57.2, U10.1 (VDD)
